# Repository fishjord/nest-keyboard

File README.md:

# Sofle Nest Keyboard

The Nest keyboard (or Sofle Nest) is a hobby project keyboard based on the sofle design. I've been
using a [Sofle Pico](soflepico.com) as my daily driver and accumulated a number of tweaks I'd like
to try out. This keyboard is the platform for that.

[!Nest Keyboard Render](images/sofle_nest_front.png)

## Basis

The Sofle Nest initial design was created by mashing the Sofle Pico PCB together with the Sofle RGB
v2.1 PCB. The Nest uses the basic layout of the Sofle Pico complete with through-hole diode
footprints, helpful silk screen component labels, and simplified LED layout. From the Sofle RGB I
took the basic promicro footprint for the MCU (modified to use KB2040 pin labels) and layout of the
OLED header.

The initial revision of the Nest adds a USB-C-like footprint for connecting the halves (in addition
to TSSR for now). This is not a true USB-C port, just the TX/RX/PWR/GND sent over a USB-C connector.
I tried to wire the connector as close to the spec as possible, using the VBUS and GND pins and
routing TX/RX over D+/D-.

v0 also includes a footprint for an FFC connector on the board for a
cirque track pad based on https://github.com/keyboard-magpie/minimal-fpc-i3c-pcb and a hotswappable
combo encoder/key switch footprint for SW25.

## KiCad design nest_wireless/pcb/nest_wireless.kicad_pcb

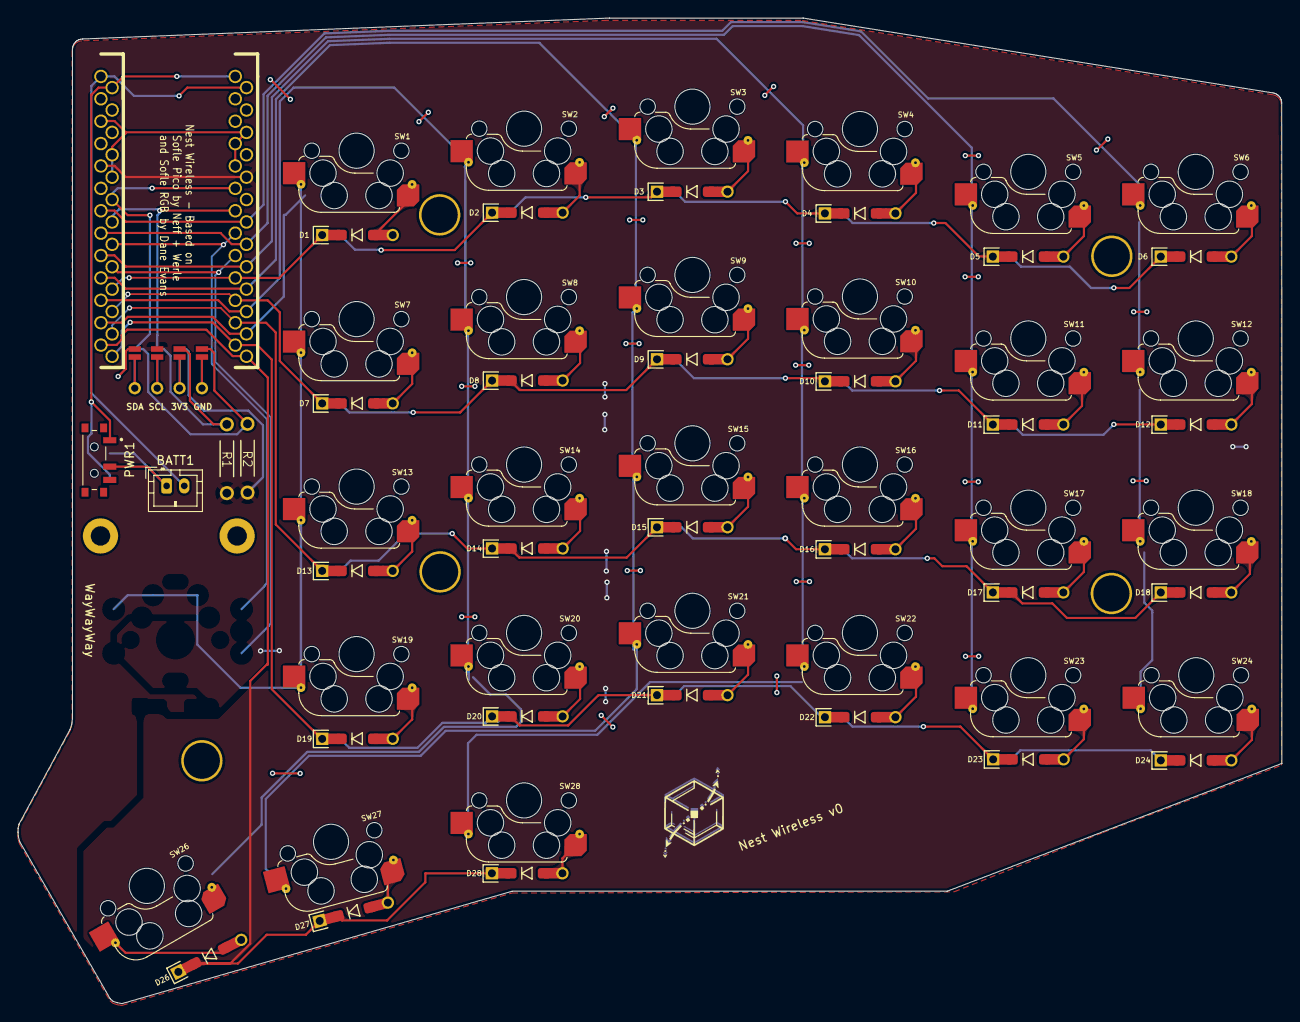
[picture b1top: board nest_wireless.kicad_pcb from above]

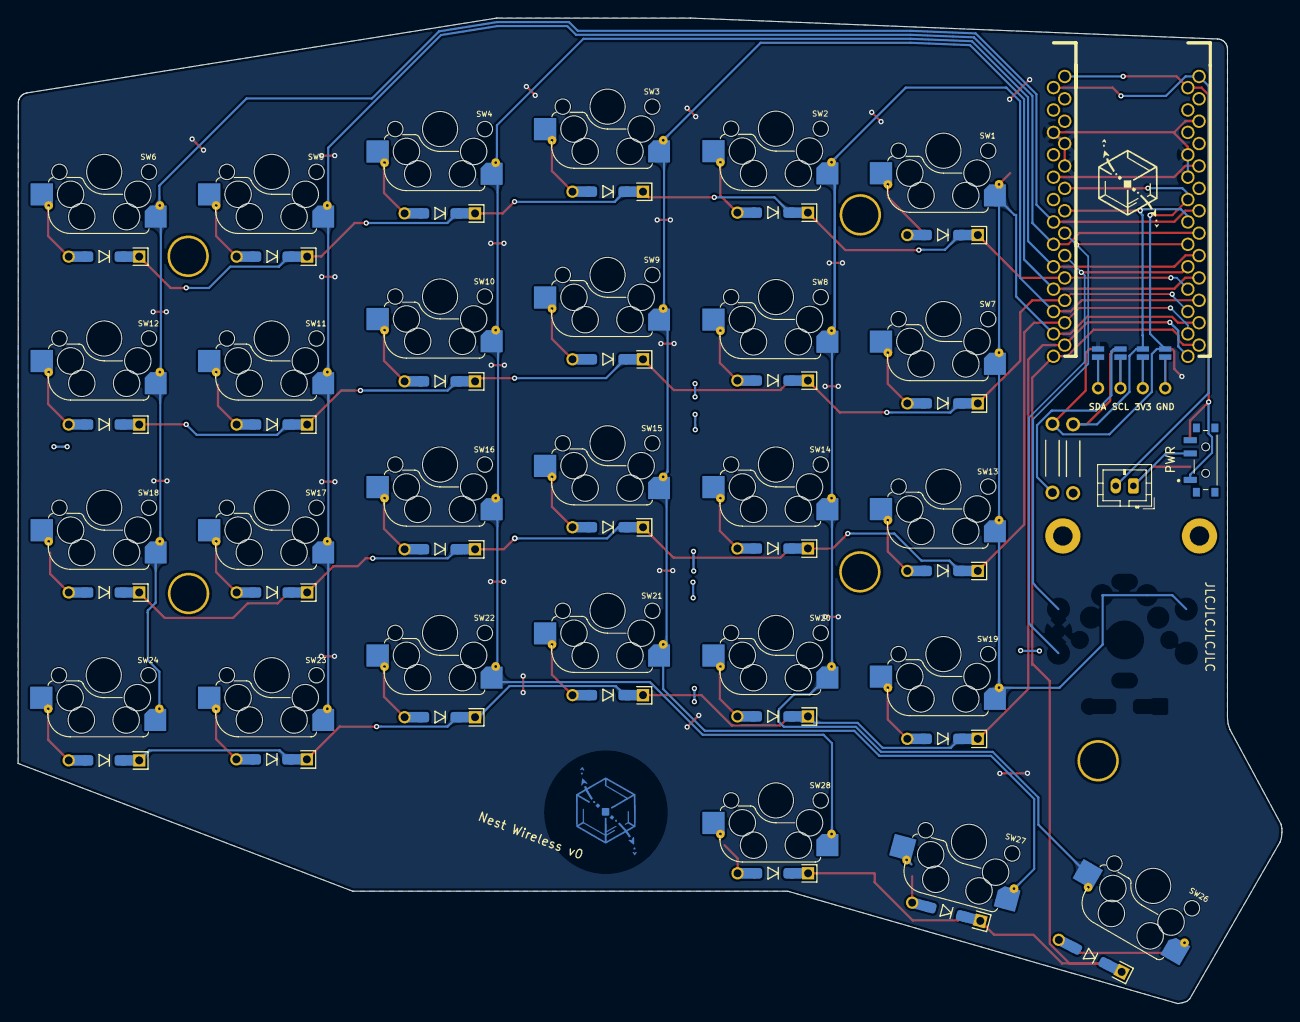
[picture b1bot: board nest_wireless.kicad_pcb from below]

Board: 2 copper layers, 143.4 x 111.8 mm, 69 parts (54 on the bottom side), 45 nets.

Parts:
BATT1: Conn_01x02; BatteryConnector
D1, D2, D3, D4, D5, D6, D7, D8, D9, D10, D11, D12, D13, D14, D15, D16, D17, D18, D19, D20, D21, D22, D23, D24, D26, D27, D28: D; D_SOD-123_DO-35_Hybrid_DoubleSided_V2
J3: Conn_01x04; OLED Header
PWR1: EG1215AA; SW_EG1215AA
R1, R2: 2.2k; Pullup Resistor
Ref**: Val**; nest_logo_b.cu
Ref**#2: Val**; nest_logo_bsilk
SW1, SW2, SW3, SW4, SW5, SW6, SW7, SW8, SW9, SW10, SW11, SW12, SW13, SW14, SW15, SW16, SW17, SW18, SW19, SW20, SW21, SW22, SW23, SW24, SW26, SW27, SW28: SW_PUSH; Cherry_MX_DS_Hotswap_v3.5.4
TH1, TH2: HOLE; M2_HOLE_PCB
TH3, TH4, TH5, TH6, TH7: HOLE; Hole from sofle for M2 posts gold rimmer
U2: kb2040; kb2040_compact

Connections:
+BATT: BATT1.1, PWR1.2
-BATT: BATT1.2, U2.14 (D-)
GND: J3.4, U2.4 (GND), U2.5 (GND), U2.16 (GND)
unnamed: D1.2 (A), SW1.2
unnamed: D2.2 (A), SW2.2
unnamed: D3.2 (A), SW3.2
unnamed: D4.2 (A), SW4.2
unnamed: D5.2 (A), SW5.2
unnamed: D6.2 (A), SW6.2
unnamed: D7.2 (A), SW7.2
unnamed: D8.2 (A), SW8.2
unnamed: D9.2 (A), SW9.2
unnamed: D10.2 (A), SW10.2
unnamed: D11.2 (A), SW11.2
unnamed: D12.2 (A), SW12.2
unnamed: D13.2 (A), SW13.2
unnamed: D14.2 (A), SW14.2
unnamed: D15.2 (A), SW15.2
unnamed: D16.2 (A), SW16.2
unnamed: D17.2 (A), SW17.2
unnamed: D18.2 (A), SW18.2
unnamed: D19.2 (A), SW19.2
unnamed: D20.2 (A), SW20.2
unnamed: D21.2 (A), SW21.2
unnamed: D22.2 (A), SW22.2
unnamed: D23.2 (A), SW23.2
unnamed: D24.2 (A), SW24.2
unnamed: D26.2 (A), SW26.1
unnamed: D27.2 (A), SW27.2
unnamed: D28.2 (A), SW28.2
SCL: J3.2, R1.2, U2.7 (D3)
SDA: J3.1, R2.2, U2.6 (D2)
SW+: PWR1.1, U2.1 (D+)
VCC: J3.3, R1.1, R2.1, U2.18 (3.3v)
col0: SW6.1, SW12.1, SW18.1, SW24.1, U2.20 (A2/28)
col1: SW5.1, SW11.1, SW17.1, SW23.1, U2.21 (A1/27)
col2: SW4.1, SW10.1, SW16.1, SW22.1, SW28.1, U2.22 (A0/26)
col3: SW3.1, SW9.1, SW15.1, SW21.1, SW27.1, U2.23 (SCK/18)
col4: SW2.1, SW8.1, SW14.1, SW20.1, SW26.2, U2.24 (MISO/20)
col5: SW1.1, SW7.1, SW13.1, SW19.1, U2.25 (MOSI/19)
row0: D1.1 (K), D2.1 (K), D3.1 (K), D4.1 (K), D5.1 (K), D6.1 (K), U2.10 (D6)
row1: D7.1 (K), D8.1 (K), D9.1 (K), D10.1 (K), D11.1 (K), D12.1 (K), U2.11 (D7)
row2: D13.1 (K), D14.1 (K), D15.1 (K), D16.1 (K), D17.1 (K), D18.1 (K), U2.12 (D8)
row3: D19.1 (K), D20.1 (K), D21.1 (K), D22.1 (K), D23.1 (K), D24.1 (K), U2.13 (D9)
row4: D26.1 (K), D27.1 (K), D28.1 (K), U2.26 (D10)

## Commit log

2025-12-29 Initial commit of the protoype 'Sofle Nest' sofle keyboard variant
2025-12-29 Create pcb and acrylic case models for the Sofle Nest.
2025-12-29 Add case foam outlines for the Sofle Nest.
2025-12-29 Fix board side and model orientation for a few footprints.
2025-12-30 Fix issues with case plates found during fabrication eval.
2025-12-30 Update acrylic plate dxfs to use millimeters instead of inches.
2025-12-30 Fix pullup resistor model to align with the holes
2025-12-30 Add renders for the pcb plates and main pcb.
2025-12-30 Add a render with the encoder in place of SW25
2026-01-03 Re-route underglow leds to put the top ones in series
2026-01-03 Update schematic to pass electrical check rules and rewrite LEDs row-wise
2026-01-03 Rewire rows and columns
2026-01-03 Rework LED footprints to have built in vias to simplify routing
2026-01-03 Fix silk screening to be more consistent across components
2026-01-04 Add a README for the nest keyboard
2026-01-06 Move 'sofle_nest' related files under a sub-directory to make space for handwired prototyping
2026-01-06 Add prototype 3d models for a fdm hand-wired case for an experimental layout
2026-01-06 Add fdm case models for the prototype handwired nest keyboard
2026-01-09 Delete sofle_nest/pcb/sofle_nest.pretty/kb2040.kicad_mod:Zone.Identifier
    Delete stray zone identifier file that accidentally got committed.
2026-01-09 Add an ignore rule for zone identifier files.
2026-01-09 Fix the left hand keyplate to have the top of the plate be printed face down.
2026-01-11 Generate lh and rh versions of all stls and delete gcode files.
2026-01-17 Add a design folder with an updated keyplate svg containing amoeba pcb outlines.
2026-01-17 Add prototype case outlines for the handwired layout
2026-01-18 Create a left and right hand backplate foam layer
2026-01-18 Regenerate prototype case files and models based on a production round
2026-01-23 Update keyplate model and foam to have more space for stabilizers
2026-01-23 Rotate SW 26+27 support plate cutout 90 degrees and regen models.
2026-01-24 Add wiring to design file and rename it to nest_keyboard
2026-02-04 Add a controller cover plate to the prototype case.
2026-02-08 Add via design file for the handwired layout.
2026-06-13 Create a slimmed down wireless version of the nest keyboard
2026-06-13 Clean up a few design rule violations
2026-06-20 Nest wireless kicad project cleanup
2026-06-24 Create an ergogen for a v1 config based on my experiences with the v0
2026-06-28 Tweak the ergogen config to move the thumb row lower and generate some prototype 3dm plates
2026-06-28 Tweak ergogen config to make it easier to generate 4 and 5 row variants
2026-06-28 Add backplate foam to the ergogen config
